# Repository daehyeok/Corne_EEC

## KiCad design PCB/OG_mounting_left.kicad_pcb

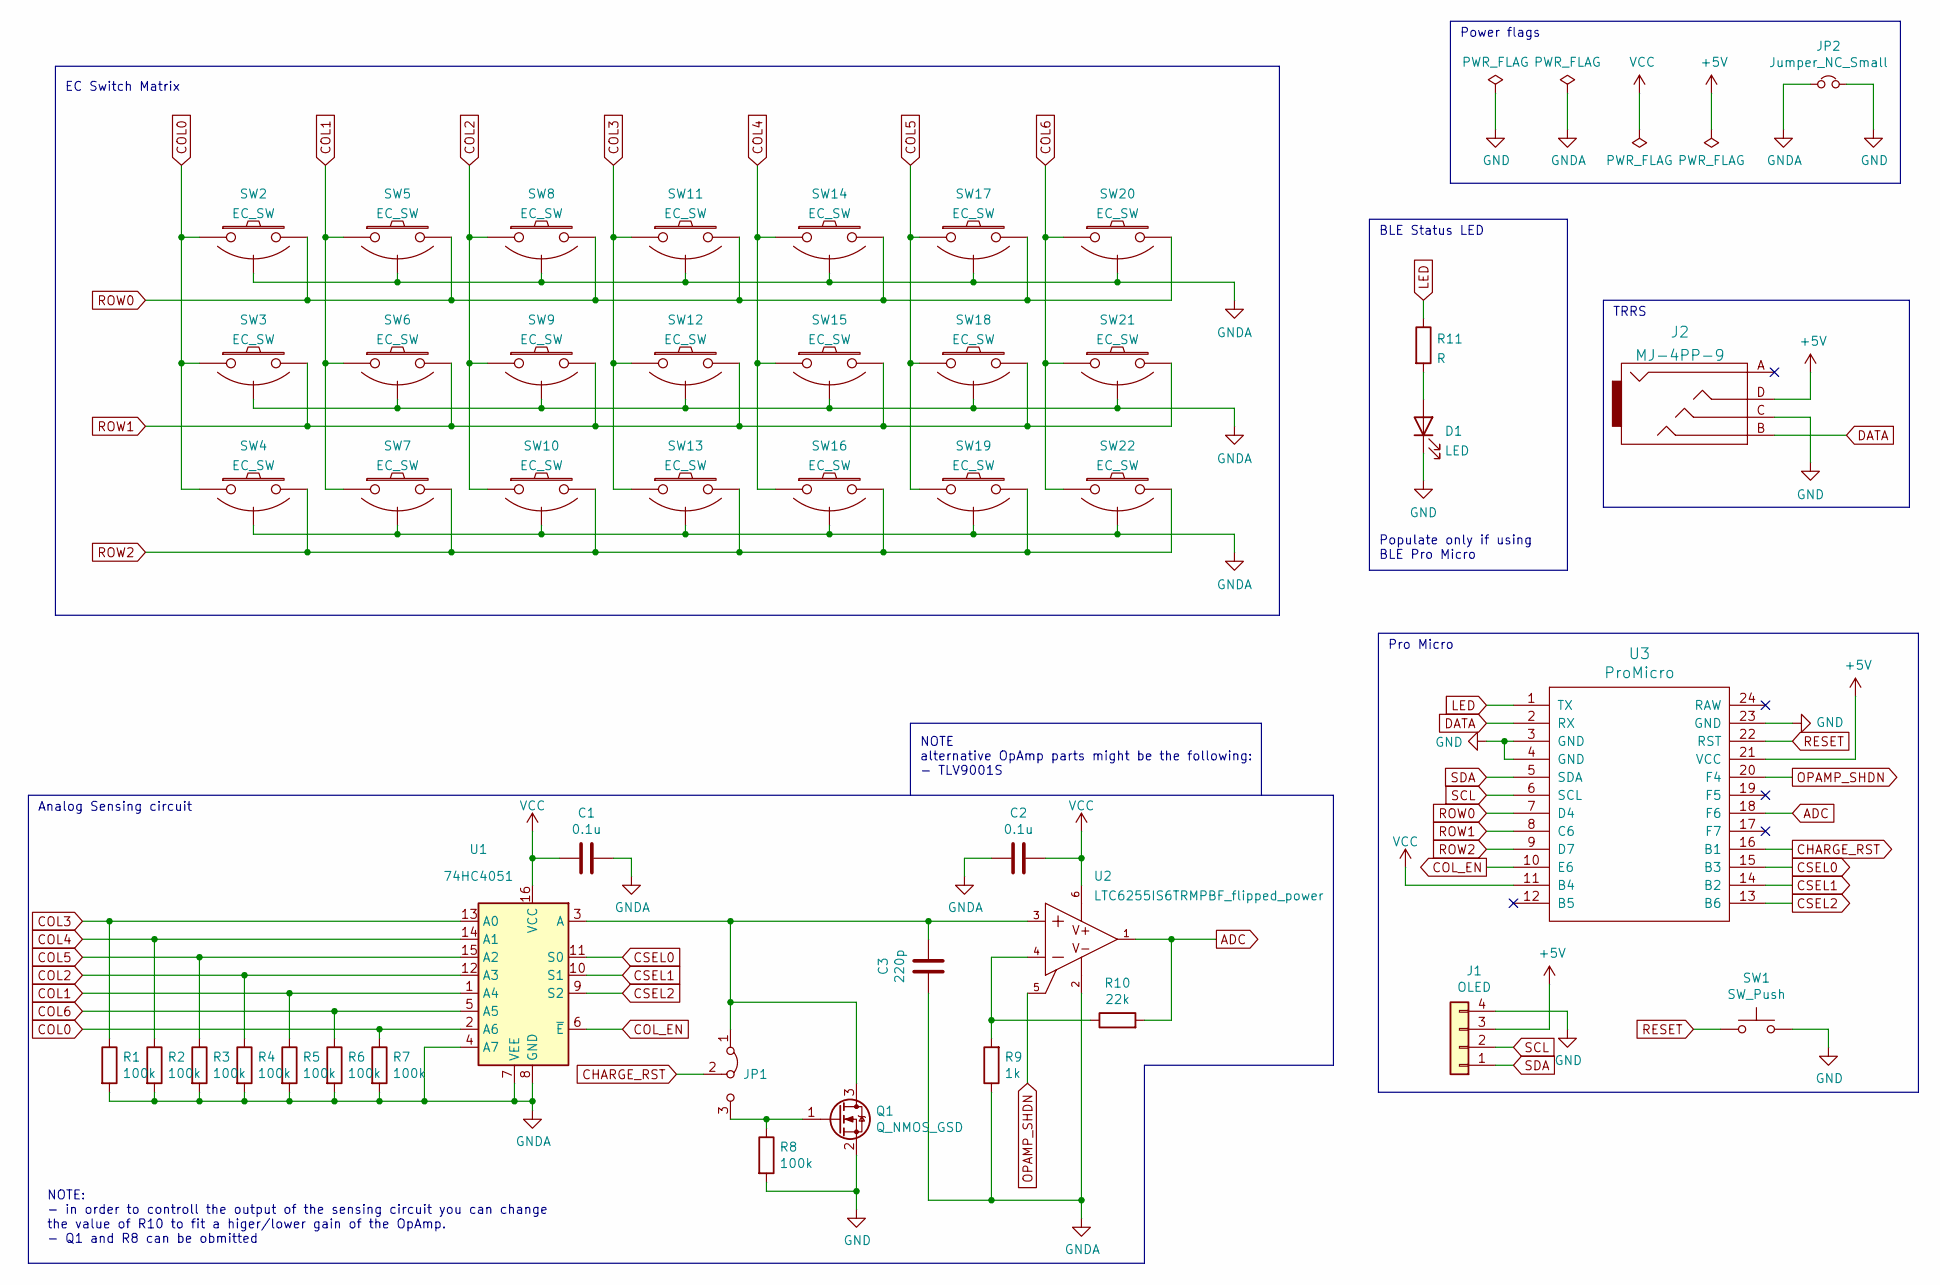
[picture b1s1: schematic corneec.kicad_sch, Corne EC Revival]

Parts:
C1, C2: 0.1u; C_0603_1608Metric_Pad1.08x0.95mm_HandSolder
C3: 220p; C_0603_1608Metric_Pad1.08x0.95mm_HandSolder
D1: LED; D_0603_1608Metric
J1: OLED; OLED_Small
J2: MJ-4PP-9; TRRS-PJ-320A-no-Fmask
JP1: Jumper_3_Bridged12; SolderJumper-3_P1.3mm_Bridged12_Pad1.0x1.5mm
JP2: Jumper_NC_Small; SolderJumper-2_P1.3mm_Bridged_Pad1.0x1.5mm
Q1: Q_NMOS_GSD; SOT-23
R1, R2, R3, R4, R5, R6, R7, R8: 100k; R_0603_1608Metric_Pad0.98x0.95mm_HandSolder
R9: 1k; R_0603_1608Metric_Pad0.98x0.95mm_HandSolder
R10: 22k; R_0603_1608Metric_Pad0.98x0.95mm_HandSolder
R11: R; R_0603
SW1: SW_Push; SW_3.5x6.0_TH
SW2, SW3, SW4, SW5, SW6, SW7, SW8, SW9, SW10, SW11, SW12, SW13, SW14, SW15, SW16, SW17, SW18, SW19, SW20, SW21, SW22: EC_SW; ecs_pad
U1: 74HC4051; TSSOP16
U2: LTC6255IS6TRMPBF_flipped_power; TSOT-23-6_HandSoldering
U3: ProMicro; Sparkfun_Pro_Micro

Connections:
+5V: J1.3, J2.D, U3.21 (VCC)
ADC: R10.2, U2.1 (OUT), U3.18 (F6)
CHARGE_RST: JP1.2 (C), U3.16 (B1)
COL0: R7.1, SW2.1, SW3.1, SW4.1, U1.2 (A6)
COL1: R5.1, SW5.1, SW6.1, SW7.1, U1.1 (A4); also elsewhere on the board
COL2: R4.1, SW8.1, SW9.1, SW10.1, U1.12 (A3); also elsewhere on the board
COL3: R1.1, SW11.1, SW12.1, SW13.1, U1.13 (A0)
COL4: R2.1, SW14.1, SW15.1, SW16.1, U1.14 (A1)
COL5: R3.1, SW17.1, SW18.1, SW19.1, U1.15 (A2)
COL6: R6.1, SW20.1, SW21.1, SW22.1, U1.5 (A5)
COL_EN: U1.6 (~E), U3.10 (E6)
CSEL0: U1.11 (S0), U3.15 (B3)
CSEL1: U1.10 (S1), U3.14 (B2)
CSEL2: U1.9 (S2), U3.13 (B6)
DATA: J2.B, U3.2 (RX)
GND: D1.1 (K), J1.4, J2.C, JP2.2, Q1.2 (S), R8.2, SW1.2, U3.3 (GND), U3.4 (GND), U3.23 (GND)
GNDA: C1.1, C2.2, C3.2, JP2.1, R1.2, R2.2, R3.2, R4.2, R5.2, R6.2, R7.2, R9.1, SW2.3 (SG), SW3.3 (SG), SW4.3 (SG), SW5.3 (SG), SW6.3 (SG), SW7.3 (SG), SW8.3 (SG), SW9.3 (SG), SW10.3 (SG), SW11.3 (SG), SW12.3 (SG), SW13.3 (SG), SW14.3 (SG), SW15.3 (SG), SW16.3 (SG), SW17.3 (SG), SW18.3 (SG), SW19.3 (SG), SW20.3 (SG), SW21.3 (SG), SW22.3 (SG), U1.4 (A7), U1.7 (VEE), U1.8 (GND), U2.2 (V-); also elsewhere on the board
LED: R11.1, U3.1 (TX)
unnamed: C3.1, JP1.1 (A), Q1.3 (D), U1.3 (A), U2.3 (+IN)
unnamed: D1.2 (A), R11.2
unnamed: JP1.3 (B), Q1.1 (G), R8.1
unnamed: R9.2, R10.1, U2.4 (-IN)
OPAMP_SHDN: U2.5 (~SHDN), U3.20 (F4)
RESET: SW1.1, U3.22 (RST)
ROW0: SW2.2, SW5.2, SW8.2, SW11.2, SW14.2, SW17.2, SW20.2, U3.7 (D4)
ROW1: SW3.2, SW6.2, SW9.2, SW12.2, SW15.2, SW18.2, SW21.2, U3.8 (C6); also elsewhere on the board
ROW2: SW4.2, SW7.2, SW10.2, SW13.2, SW16.2, SW19.2, SW22.2, U3.9 (D7); also elsewhere on the board
SCL: J1.2, U3.6 (SCL)
SDA: J1.1, U3.5 (SDA)
VCC: C1.2, C2.1, U1.16 (VCC), U2.6 (V+), U3.11 (B4)

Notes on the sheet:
TRRS
NOTE alternative OpAmp parts might be the following: - TLV9001S
Populate only if using BLE Pro Micro
Pro Micro
NOTE: - in order to controll the output of the sensing circuit you can change the value of R10 to fit a higer/lower gain of the OpAmp. - Q1 and R8 can be obmitted
EC Switch Matrix
Analog Sensing circuit
BLE Status LED
Power flags

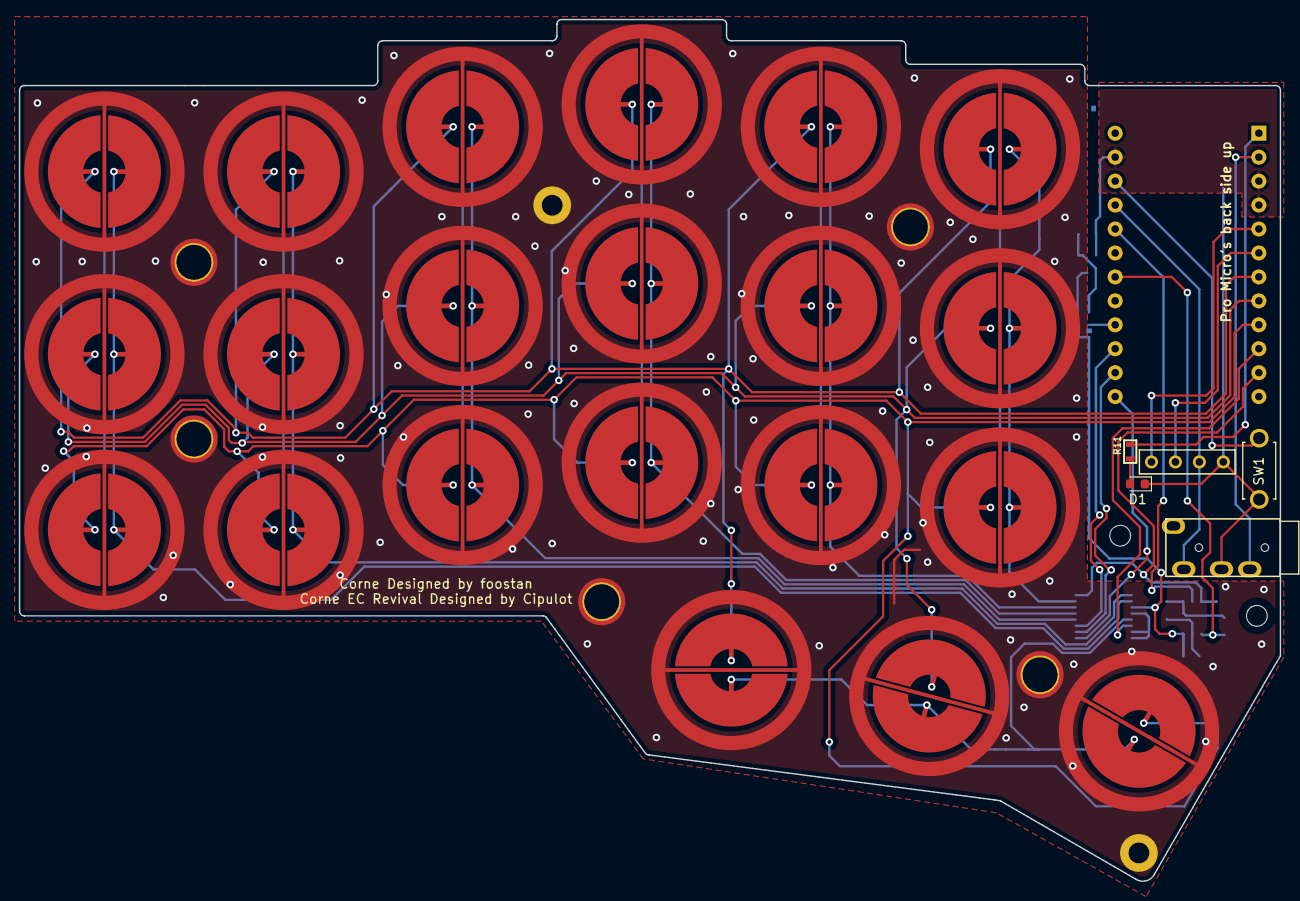
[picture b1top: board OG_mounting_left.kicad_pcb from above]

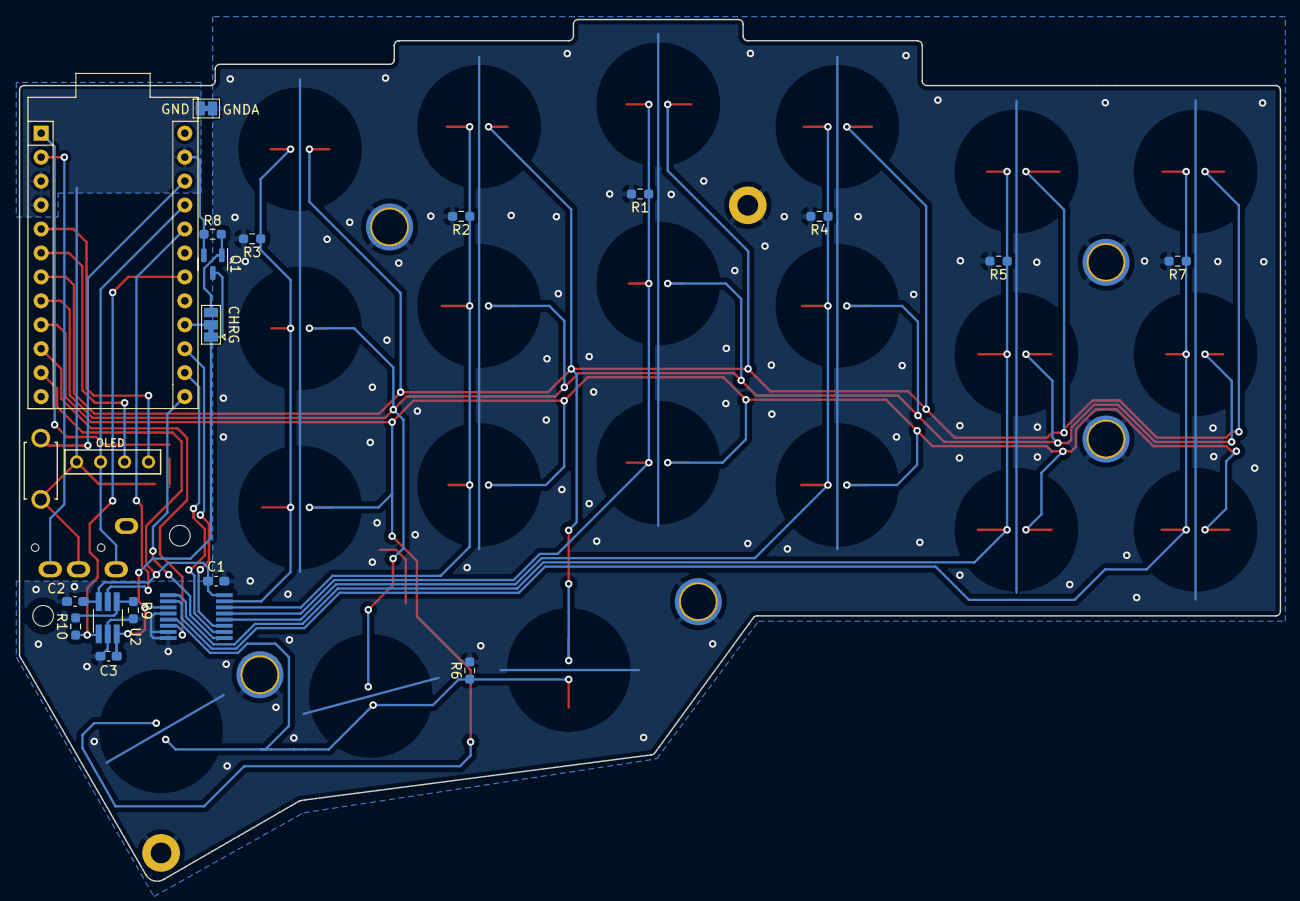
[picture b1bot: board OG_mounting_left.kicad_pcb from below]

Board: 2 copper layers, 133.8 x 91.4 mm, 46 parts (19 on the bottom side), 30 nets.

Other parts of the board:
H22: MountingHole; HOLE_M2
SWe: EC_SW; ecs_pad
SWe#2: EC_SW; ecs_pad

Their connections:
COL1: SWe#2.1; also elsewhere on the board
COL2: SWe.1; also elsewhere on the board
GNDA: SWe.3 (SG), SWe#2.3 (SG); also elsewhere on the board
ROW1: SWe.2; also elsewhere on the board
ROW2: SWe#2.2; also elsewhere on the board

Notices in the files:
PCB/OG_mounting_left.kicad_pcb:
Copyright © 2021 Cipulot
MIT License
